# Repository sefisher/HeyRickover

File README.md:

# HEY RICKOVER PROJECT GIT

The is the git repository for the Hey Rickover Project. This is a work in progress to explore [Atomic14's awesome DIY Alexa example](https://github.com/atomic14/diy-alexa) and look for ways to remove cloud/internet dependency further (e.g., eliminate Wit.ai) and play with developing harware to make a custom low cost device. Below is the initial project announcement/invitation. The code files above are structured top split the work into different areas of interest (aligned to the project sections described below). Each folder should have a README.md file to help people get started from "bare metal" and learn about that part of the project.  

# Initial Project Overview:

Inviting you and anyone interested to join a project team and contribute to a fun development project called “Hey Rickover”.  Summary of the why/what is below. If you have questions or would like to join send me a note.  After this initial invite all communications will be done in a Slack workspace that we’ll set up for team communications and collaboration – so please tell me if you want to be invited to our Slack Workspace. (For those of you who have already told me you want to join please send me an email address to use for Slack if you haven’t already done so.) Joining us in Slack doesn’t commit you to do anything – but we’ll probably end up using that space/app for future projects as well – so I encourage you to come check it out.  We’ll have various channels setup for the different aspects of development. You can also contact me via personal email.  This is intended to be a fun at home project with most of the work done after hours.

This project is certainly feasible – [here is a video tutorial of something that is almost exactly what we are looking for](https://github.com/atomic14/diy-alexa).  Maybe we don’t need a speaker; we certainly need a cool package and PCB; and we would prefer to not use Wit.ai as an interpreter to keep our home automation out of the cloud – but who knows.  Anyway we’ve got a lot of stuff in the DIY space to start from and can focus on optimizing our design and making it fit our specific needs and then packaging the results just in time for holiday shopping (what a great gift idea!!).   

**Baseline Tutorial:** https://www.youtube.com/watch?v=re-dSV_a0tM

**Project General Goal:**  Building a device to capture voice commands for use in home automation that does not rely on any internet services.

**Use Case:** Enable affordable voice control at home without privacy/security concerns associated internet based commercial services like Google Home (Hey Google), Amazon Echo (Alexa), or Apple Homekit (Hey Siri).

.

**Learning Goals/Topics:** Home Automation Platforms, Artificial Intelligence (trigger word detection and natural language understanding), Software Development and Programming, Communication Protocols, Control System and Network Security, Lightweight Processors and “Internet of Things (IoT)”, Printer Circuit Board design and Manufacturing, Audio Processing, 3D printing and Computer Aided Design for Additive Manufacturing, Open Source Applications, Developing Tutorials and Video Content.

# Specific Project Goals:

*--Cost:* Targeting <$15 to make each device (case, parts, etc); minimize the labor to assemble and program – but labor costs can be excluded.  Stretch goal: Include AC-DC power conversion hardware in cost (otherwise rely on a USB adapter being provided).

*--Internet Independence:*  Each device should be able to detect a customizable trigger (“Hey Rickover”) and then capture and transmit text from the following voice command.  The trigger word detection and voice-to-text transcoding shall occur on the device itself. Stretch goal: Include Natural Language Understanding (figure out what a user intends) detection in on-premises device/server (in lieu of using Wit.ai or other cloud service).

*--Power:* Device is designed to listen so should be light and allowing “hanging” off any 120V outlet – either hooked onto USB wall adapter or using its own plug.  Stretch goal: include low-cost and high efficiency (>85%) power conversion from 120V AC.

*--Device Output:* The device will provide text commands as output to be interpreted and used by home automation systems.  Stretch Goal: Devices could determine “quality” (loudness/accuracy measures) and negotiate with other devices to deconflict audio commands heard by multiple devices so only one version of what is heard is passed on.

*--System Output:* A server (Raspberry Pi, virtual machine, etc) should determine the intent (Natural Language Understanding (NLU)) and translate natural speech into machine executable commands. Stretch Goal:  Do NLU on the device itself.

# Project Areas and Phases:
**You don’t need to know it all or do it all.  The project will need people to work in small teams (and team leaders) to explore and then deliver in different areas.  The following are expected project areas and stages of development.  You are free to jump in or out and contribute however best suits you.**

.

# Topics for Early Exploration and Likely Tasks in Project Areas:

**Electronic Design/Manufacturing:** 

--Microprocessor Selection – choosing the core platform based on cost/capability/reliability/power-consumption (e.g., Pi-Zero, ESP32, etc).

--Should we make a simple PCB and solder in/on selected parts?  Should we design a PCB and have a manufacturer assemble the whole board including component placement and soldering?

--Select PCB design tools

**Power:**

--Should we assume user provided wall-adapters (impacts case design – need to hang off of USB; impacts efficiency and product value)?

--Should we use our expertise in power electronics and make a high-efficiency/low-cost converter and plug the device in directly?

--Measure efficiency and power consumption – what are reasonable design goals for designing power conversion into device (cost, efficiency, etc)?

**Audio:**

--Microphone selection – I2S output from a MEMs mic seems like the best option – but are there other choices? Integrated board or just the mic in our own custom circuit?

--Should we provide speaker for device response?  Or simple buzzer (piezo speaker) to “beep” and acknowledge trigger-word and end of recording a command.

--Provide input to package/case design team to ensure good sounds pickup and sensitivity.

Trigger Word Detection and Voice to Text Capture:

--This will be done on the device we build directly; but training a lightweight AI model with an uncommon trigger word may be hard.  Should we use something other than “Hey Rickover”?

--Select software and approach for light-AI-framework to detect trigger word on low cost IoT microprocessors.

--Developing work flow and nodal network to allow high accuracy custom trigger-word detection.

**Natural Language Understanding (NLU):**

--Investigate options for NLU AI-frameworks to convert transcribed human sentences to intended actions (e.g., Wit.ai, RASA, Snips, Almond, etc).

--Goal is all on-premises (local devices on your home network) without reliance on cloud; but consider privacy, reliability, speed, performance of options.

--Determine feasibility of allowing user options and programmable settings to select among various NLU processors.

Software Development and App Integration:

--Select tools for work flow and team collaboration.

--Identify best practices for coding and coordinate development language choice for various system sections.

**Packaging Design:**

--Select CAD design tools for 3D printed prototyping and design collaboration (e.g., tinkercad.com, fusion 360).

--Prototype and 3D print flexible designs to hold a circuit board with or without onboard power (e.g., integrated plug or for a wall-adapter).

--Coordinate with potential users and other design teams on goals.

--Explore options for injection molding and manufacturing final product vs posting 3D model for DIY manufacturing with 3D printers.

**Security:**

--Explore vulnerabilities in fundamental design.

--Suggest security enhancements in system that balance availability, confidentiality, and integrity of system and data.

--Explore vulnerabilities in design process and our “vendor base”.

**Documenting and Publishing:**

--Plan out how to publish tutorials and share lessons learned across all areas.

--Produce videos, websites, etc.

--Decide if the final product should be made available for purchase at cost.

--Provide input on any “branding” logos, etc.

**Home Automation Integration:**

--Develop the baseline “use case” to share as an example.

--Work across the team to help integrate the device into different home-automation environments.

--Provide support, capture best practices, and feedback improvement needs for product design to make it easier to use and more flexible.

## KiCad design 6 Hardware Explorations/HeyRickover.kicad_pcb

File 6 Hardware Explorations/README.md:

**WORKING ON HARDWARE**

This is where to store info on working with the the various hardware projects to include making a custom PC board, 3D modeling and developing packaging, and notes on component selection.

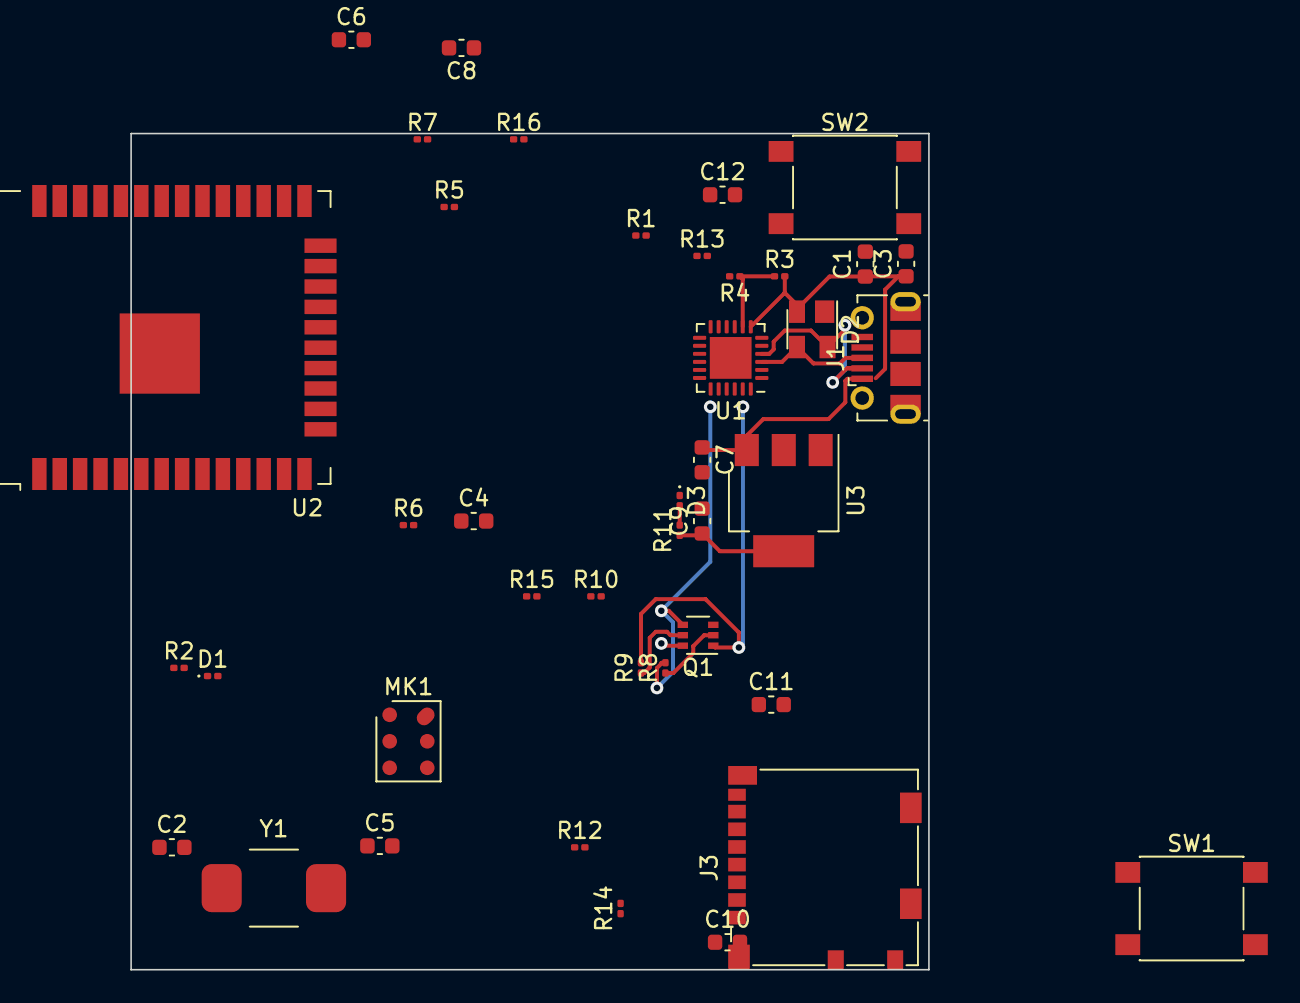
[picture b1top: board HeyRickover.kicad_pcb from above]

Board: 2 copper layers, 49.7 x 52.1 mm, 41 parts (0 on the bottom side), 32 nets.

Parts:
C1, C3, C6: 10uF; C_0603_1608Metric
C2, C5: 27pF/50V; C_0603_1608Metric
C4, C12: 0.1uF/50V; C_0603_1608Metric
C7, C9: 1uF; C_0603_1608Metric
C8: 0.1uF; C_0603_1608Metric
C10, C11: 10uF/25V; C_0603_1608Metric
D1: LED_IO23_W; LED_0201_0603Metric
D2: SP0503BAHT; SOT-143
D3: Led_PWR_G; LED_0201_0603Metric
J1: USB_B_Micro; USB_Micro-B_Molex-105017-0001
J3: Micro_SD_Card; microSD_HC_Molex_104031-0811
MK1: MP45DT02; ST_HLGA-6_3.76x4.72mm_P1.65mm
Q1: BC847BS; SOT-363_SC-70-6
R1, R5: 10k/1%; R_0201_0603Metric
R2, R7, R10, R11, R15, R16: 470; R_0201_0603Metric
R3: 22.1k; R_0201_0603Metric
R4: 47.5k; R_0201_0603Metric
R6, R8, R9, R12, R13, R14: 10k; R_0201_0603Metric
SW1, SW2: SW_Push; SW_Push_1P1T_NO_6x6mm_H9.5mm
U1: CP2102N-A01-GQFN24; QFN-24-1EP_4x4mm_P0.5mm_EP2.6x2.6mm
U2: ESP32-WROOM-32D; ESP32-WROOM-32
U3: AMS1117-3.3; SOT-223-3_TabPin2
Y1: 32.768KHz; Crystal_SMD_TXC_AX_8045-2Pin_8.0x4.5mm

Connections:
+3V3: C6.1, C8.1, C9.1, C10.1, C11.1, J3.4, MK1.6, R1.2, R2.1, R6.2, R11.1, R12.1, R13.1, R14.1, U3.2
+5V: C1.1, C3.1, C7.1, D2.2, J1.1, R3.2, U1.7, U3.3
D+: D2.3, J1.3, U1.3
D-: D2.4, J1.2, U1.4
DTR: Q1.4, R8.2, U1.23
EN: C4.1, Q1.6, R6.1, R15.1, U2.3
GND: C1.2, C2.2, C3.2, C4.2, C5.2, C6.2, C7.2, C8.2, C9.2, C10.2, C11.2, C12.2, D2.1, D3.1, J1.5, J1.6, J3.6, J3.9, MK1.1, MK1.3, R4.2, SW1.1, SW2.1, U1.2, U1.25, U2.1, U2.2, U2.15, U2.38, U2.39, U3.1
IO0: Q1.3, R1.1, R5.1, U2.25
IO2: R5.2, U2.24
IO12-MISO: J3.7, U2.14
IO13-CS: J3.2, R14.2, U2.16
IO14-CLK: J3.5, R12.2, U2.13
IO15-MOSI: J3.3, R13.2, U2.23
IO18: R16.1, U2.30
IO23: D1.1, U2.37
IO25-MIC_SEL: MK1.2, U2.10
IO26-MIC_CLK: MK1.4, U2.11
IO27-MIC_DATA: MK1.5, U2.12
IO32: C2.1, U2.8, Y1.1
IO33: C5.1, U2.9, Y1.2
unnamed: C12.1, R16.2, SW2.2
unnamed: D1.2, R2.2
unnamed: D3.2, R11.2
unnamed: Q1.2, R8.1
unnamed: Q1.5, R9.1
unnamed: R3.1, R4.1, U1.8
unnamed: R15.2, SW1.2
RTS: Q1.1, R9.2, U1.19
RXD: R7.2, U2.34
RXD_CP2102: R10.1, U1.20
TXD: R10.2, U2.35
TXD_CP2102: R7.1, U1.21

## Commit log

2021-07-20 test
2021-07-27 Setting up folder structure
2021-07-27 chunk 1 sounds
2021-07-27 chunk 2 sounds
2021-07-27 chunk 3 sounds
2021-07-27 last chunk sounds
2021-07-27 hardware pics
2021-07-27 Create ESP32_with_microphone.sch
    First try at a simple board that has an ESP-WROOM processor with USB enabled programming and power along with a microphone. Still working on the PCB routing. Parts (other than the headers which are o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
2021-07-27 Added symbol and footprint libraries
    Realized I needed to add the libraries, too
2021-07-28 firmware
2021-07-28 Shifted circuit design to subdirectory
2021-07-28 Deleted outdated and wrong PCB layout
2021-08-08 Create gitignore
2021-08-15 Update Training for "Rickover" with more files.
2021-08-21 Shifted to EasyEDA
2021-08-21 Added 3D-model in STL format
2021-08-21 Added board image
2021-08-21 Added files for boards ordered on 8/21/21
2021-09-11 Modifications to 8/21/2021 board.
    Disables SDCard reader, but enables flashing. IO12 and IO15 need to be disconnected from the pull-up resistors
2021-09-12 Initial board design ordered (#2)
    * Shifted to EasyEDA
    * Added 3D-model in STL format
    * Added board image
    * Shifted to EasyEDA
    * Added files for boards ordered on 8/21/21
    * Modifications to 8/21/2021 board.
2021-09-18 Added test software for LED/buzzer and another for the SDCard interface
    1. Quick and dirty test of LED/Buzzer to flash/buzz about 1/second.
    2. SD Card test assumes MISO and MOSI moved to IO16 and IO17
2021-09-25 Update BoardTest.ino
    Added button control for LED
2021-10-02 Updated to include board modification details
2021-10-02 Update BoardTest.ino
    Changed so buzzer is controlled by switch, not the LED
2021-10-19 Corrected error on back side trace cuts
    Backside cut image was shifted, which led to cutting wrong trace
2021-12-31 Added Gen2 Board
    Removes SD card reader.
    Removes USB interface from Gen2 Board and adds separate programming board design.
    Adds 8 outputs level shifted to 5V.
    Pin selections for buttons, buzzer, and LED changed.
